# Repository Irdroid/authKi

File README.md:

# Open Source Crypto Authentication USB Dongle

Irdroid authKi is a Open Source crypto Authentication USB Dongle (Open source Hardware ID - BG000091), with built-in hardware support for Asymmetric Sign, Verify, Key Agreement for ECDSA - Elliptic curve digital signature algorithm, ECDH - Elliptic Curve Diffie-Hellman and NIST Standard P256 Elliptic Curve Support,  thanks to the built-in Cryptographic Co-Processor with Secure Hardware-Based Key Storage - ATECC608B by Microchip.

USB 2.0 Interface (and optional USB-C) to the host system with built-in drivers for GNU Linux. The authKi is targeted for use in GNU Linux, the ATECC608B crypto element inside the authKi can be accessed via libusb in MS Windows and Mac OS (Still work in progress). The device will show-up on the host system as a I2C sysfs entry, which is then used by the Microchip’s cryptoauthlib for communication with the authKi dongle.

## Hardware support for:

- Asymmetric Sign, Verify, Key Agreement:
- ECDSA: FIPS186-3 Elliptic Curve Digital Signature
- ECDH: FIPS SP800-56A Elliptic Curve Diffie-Hellman
- NIST Standard P256 Elliptic Curve Support

## Symmetric Algorithms:

- SHA-256 & HMAC Hash including off-chip context save/restore
- AES-128: Encrypt/Decrypt, Galois Field Multiply for GCM

## Networking Key Management Support:

- Turnkey PRF/HKDF calculation for TLS 1.2 & 1.3
- Ephemeral key generation and key agreement in SRAM
- Small message encryption with keys entirely protected

## Software Support:

- Microchip’s Cryptoauthlib ( provides API and examples for interfacing with the authKi
- Eclet - a commandline tool to sign verify export public keys
- Other examples in the Irdroid’s authKi Github repository

## Example use:

- SSH authentication with a remote system via ECDSA keypairs ( your private key never leaves the hardware secure element e.g the AuthKi)
- ECDSA elliptic curve authentication with git / GitHub ( your private key never leaves the hardware secure element e.g the AuthKi)
- Digital Signature and Verification of files via Ellliptic Curve Algorithms (ECDSA/ECDSH)
- Developing Secure Crypto Wallets for Bitcoin / Ethereum
- Experimenting with the Microchip’s Cryptoauthlib for interfacing with the device.

## Where to start?

### 1. Clone this repository: 
```javascript
git clone --recurse-submodules https://github.com/Irdroid/authKi.git
```
This will checkout the repo and all submodules. You can then compile and install the cryptoauthlib library localted in /Software/Cryptoauthlib/
**You can also download a pre-built release package from the "releases" section above**.
    
### 2.  Install OpenSC:
```javascript
sudo apt install opensc
```
Check if the sysfs /dev/i2c-x entry for the device is created (After you plug the authKi to your system issue dmesg, and see if the /dev/i2c-x is assigned), if not then you may need to issue:

```
sudo modprobe i2c-dev
```
The above will load the kernel module for i2c dev sysfs

### 4. Set **udev rules** 
(If you are compiling from source | **You can skip this step if you are installing a prebuilt cryptoauthlib package from the releases section above**), so that the authKi will always get the same i2c interface number as a sysfs entry 
    - Create a file in /etc/udev/rules.d/11-tiny.rules with the content : 
```javascript 
   ACTION=="add|change", SUBSYSTEM=="i2c-dev", ATTRS{idVendor}=="0403", ATTRS{idProduct}=="c631", SYMLINK+="i2c-20"
```
### 5. Create / Edit /var/lib/cryptoauthlib/0.conf
Add the following content ( If you are compiling / installing from source)
```javascript 

# Reserved Configuration for a device
# The objects in this file will be created and marked as undeletable
# These are processed in order. Configuration parameters must be comma
# delimited and may not contain spaces

# Set a label for this slot (optional) - will default to <slot>ABC so
# 0.conf will have a default label 00ABC
label = 00ABC

# Configure the device interface for an enabled HAL
# hid,i2c,<address>
# i2c,<address>,<bus>
# spi,<select_line>,<baud>
interface = i2c,6C,20

# Configure the device type - base part number (optional)
device = ATECC608B-TFLXTLS

#Configure open slots for additional pkcs11 objects (optional)
#freeslots = 1,2,3
freeslots = 2,3,4,5
# Manually configure keys into device locations (slots/handles)

# Slot 0 is the primary private key
object = private,device,0
#object = private,device,0
# Slot 15 is a public key
#object = public,root,15
```
### 6. Configure SSH:
Edit /home/your_user/.ssh/config and add:
```javascript 
PKCS11Provider /usr/lib/libcryptoauth.so
```
The above will configure the cryptoauthlib as a PKCS11 Provider for All SSH connections. To configure the use of the library and the authki for specific connection add the following (for example for GitHub authentication in ./ssh/config)

```javascript 
Host github.com
 PKCS11Provider /usr/lib/libcryptoauth.so
 Port 22
 User youruser
```
This way if you have multipl authentication dongles, and/or smartcards you can specify which connection will use the relevant authentication key/smartcard

### 7. Export the ECDSA Public key from the authKi
```javascript
ssh-keygen -D /usr/lib/libcryptoauth.so
```
### 8. Use the authKi for SSH Authentication / Github GIT+SSH
The above command will print your public ECDSA key in the console, the key is suitable for usage in a remote server authorized_keys file or with Github
After putting the public key into a remote system , you can ssh into it, while your authKi is inserted in your computer.

### 9 Configuring authKi for use with the Eclet

1. Compile and install the Ecltet, the source is located in /Software/Eclet

#### random
```bash
eclet random
62F95589AC76855A8F9204C9C6B8B85F06E6477D17C3888266AEE8E1CBD65319
```
#### serial-num
```bash
eclet serial-num
0123XXXXXXXXXXXXEE
```
X's indicate the unique serial number.

#### get-pub
```bash
eclet get-pub
04EED1CB629CF87F8BF6419986F990B92EA3DFA14CDAF70EB3E8DA8F9C9504DBC5B040D6480E88F895E9E1D4477970329B060450C80E1816EFED7B0FA49868CAEB
```
One can get the public key at any time calling the command get-pub. In case the public key of a specific slot has to be called use the parameter -k.

```bash
eclet get-pub -k 0
04EED1CB629CF87F8BF6419986F990B92EA3DFA14CDAF70EB3E8DA8F9C9504DBC5B040D6480E88F895E9E1D4477970329B060450C80E1816EFED7B0FA49868CAEB
```

#### sign
```bash
eclet sign -f ChangeLog
3BAEB5705D8765B34B389F1768BAC783FCA786AB64A760D10DD133C86E5892A7A790E424C8E1540551C99FBE4F9F531B504A6004F08F3E0D4E42E96BBDE5C179
```

Performs an ECDSA signature. Data can be specified as a file with the `-f` option or passed via `stdin`. The data will be SHA256 hashed prior to signing. The result is the signature in the format: R + S.

#### verify
```bash
eclet verify -f ChangeLog --signature C650D1A30194AD68F60F40C321FB084F6177BEDAC74D0F0C276ED35B00249AC8CF3E96FB7AB14AA48223FBA2E5DD9BCAE232BF963755C42F8FD9BD77FC145D41 --public-key 049B4A517704E16F3C99C6973E29F882EAF840DCD125C725C9552148A74349EB77BECB37AA2DB8056BAF0E236F6DCFEC2C5A9A0F23CEFD8A9DC1F4693718E725D2
```

Verifies an ECDSA signature using the device. You specify the data (which will be SHA256 hashed), the signature (R+S), and the public key (0x04+X+Y). Returns a `0` exit code on success.

#### offline-verify-sign
```bash
eclet offline-verify-sign -f ChangeLog --signature C650D1A30194AD68F60F40C321FB084F6177BEDAC74D0F0C276ED35B00249AC8CF3E96FB7AB14AA48223FBA2E5DD9BCAE232BF963755C42F8FD9BD77FC145D41 --public-key 049B4A517704E16F3C99C6973E29F882EAF840DCD125C725C9552148A74349EB77BECB37AA2DB8056BAF0E236F6DCFEC2C5A9A0F23CEFD8A9DC1F4693718E725D2
```
#### 10. There are other examples in the cryptoauthlib directory for other functionalities such as AES128 enclode/decode, SHA-256 tests and examples and more. 

### authKi unit's are available for purchase from Tindie - Click on the Tindie Logo below to see product details and pricing
<p align="center" width="30%">

</p>

The authKi repository and and the authKi website were pushed to GitHub, by using the Irdroid's authKi ECDSA Keypair

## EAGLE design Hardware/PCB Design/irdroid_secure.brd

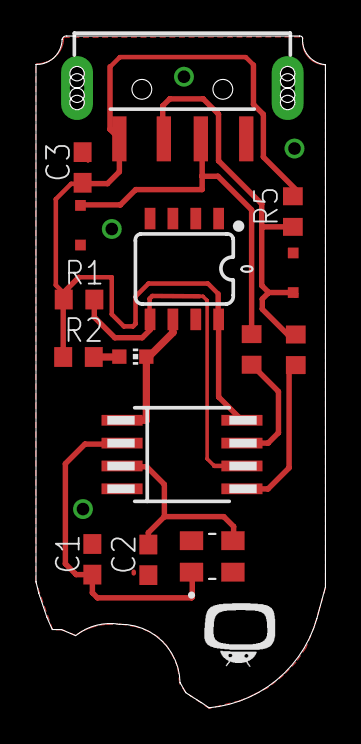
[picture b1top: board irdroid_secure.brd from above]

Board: 2 copper layers, 16.1 x 37.3 mm, 16 parts (0 on the bottom side), 11 nets.

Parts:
0: Crypto; SO08
C1, C2, C3: C0603
D1, D2: SOD323-R
J1: USB_A_SMT_MALE; USB-A-SMT-MALE
LED1: CHIP-LED0603
MC: ATTINY45V-10S; SOIC8_EIAJ_208MIL
R1, R2, R3, R4, R5: R0603
U$2: IRDROIDLOGO
Y1: ABM8-16.000MHZ-B2-T; XTAL_ABM8-16.000MHZ-B2-T

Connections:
GND: 0.4, C1.2, C2.1, C3.2, D1.A, D2.A, J1.GND1, J1.SHLD1, J1.SHLD2, MC.4, Y1.2, Y1.4
unnamed: C1.1, MC.2, Y1.1
unnamed: C2.2, MC.3, Y1.3
unnamed: 0.5, MC.6, R1.2
unnamed: 0.6, LED1.C, MC.1
unnamed: MC.5, R3.2
unnamed: MC.7, R4.2
unnamed: D2.C, J1.D-1, R3.1, R5.1
unnamed: LED1.A, R2.2
unnamed: D1.C, J1.D+1, R4.1
VCC: 0.8, C3.1, J1.VBUS1, MC.8, R1.1, R2.1, R5.2

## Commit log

2022-12-03 Initial commit
    Hardware, PCB Design, packaging, enclosure
2022-12-08 Added VUSB firmware source
    Added VUSB firmware source
2022-12-08 Added hi-res images
    Added hi-res images
2022-12-08 Added low res
    Added low res
2022-12-08 Moved top and bottom case holders into a directory
2022-12-08 Added Cryptoauthlib
2022-12-08 Added EClet
2022-12-11 Added additional details in Readme.md for authKi/Smartcards coexistance
2022-12-11 Create CNAME
2022-12-12 Added GitHub link
2022-12-12 Edit readme
2022-12-12 Update CNAME
2022-12-12 Some polishing of the website/readme.md
2022-12-12 Added theme
2022-12-12 Added dinky
2022-12-12 Added better image for the website
2022-12-12 Update site/readme
2022-12-12 Readme.md image size 55
2022-12-13 Typo readme
2022-12-13 removed fork svg
2022-12-13 Update Readme.md
    Add sysfs information
2022-12-13 Update Readme.md
    Add MS Windows and Mac OS information
2022-12-13 Update Readme.md
    Add Tindie logo
2023-01-05 Added OSHW Branding materials
    Added Open Source Hardware Branding materials
2023-01-05 Update Readme
    Update Readme
2025-10-03 Added Cryptoauthlib0.2, needed to compile EClet application

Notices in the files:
parts and their libraries:
SparkFun-Connectors: Licensing: Creative Commons ShareAlike 4.0 International - https://creativecommons.org/licenses/by-sa/4.0
